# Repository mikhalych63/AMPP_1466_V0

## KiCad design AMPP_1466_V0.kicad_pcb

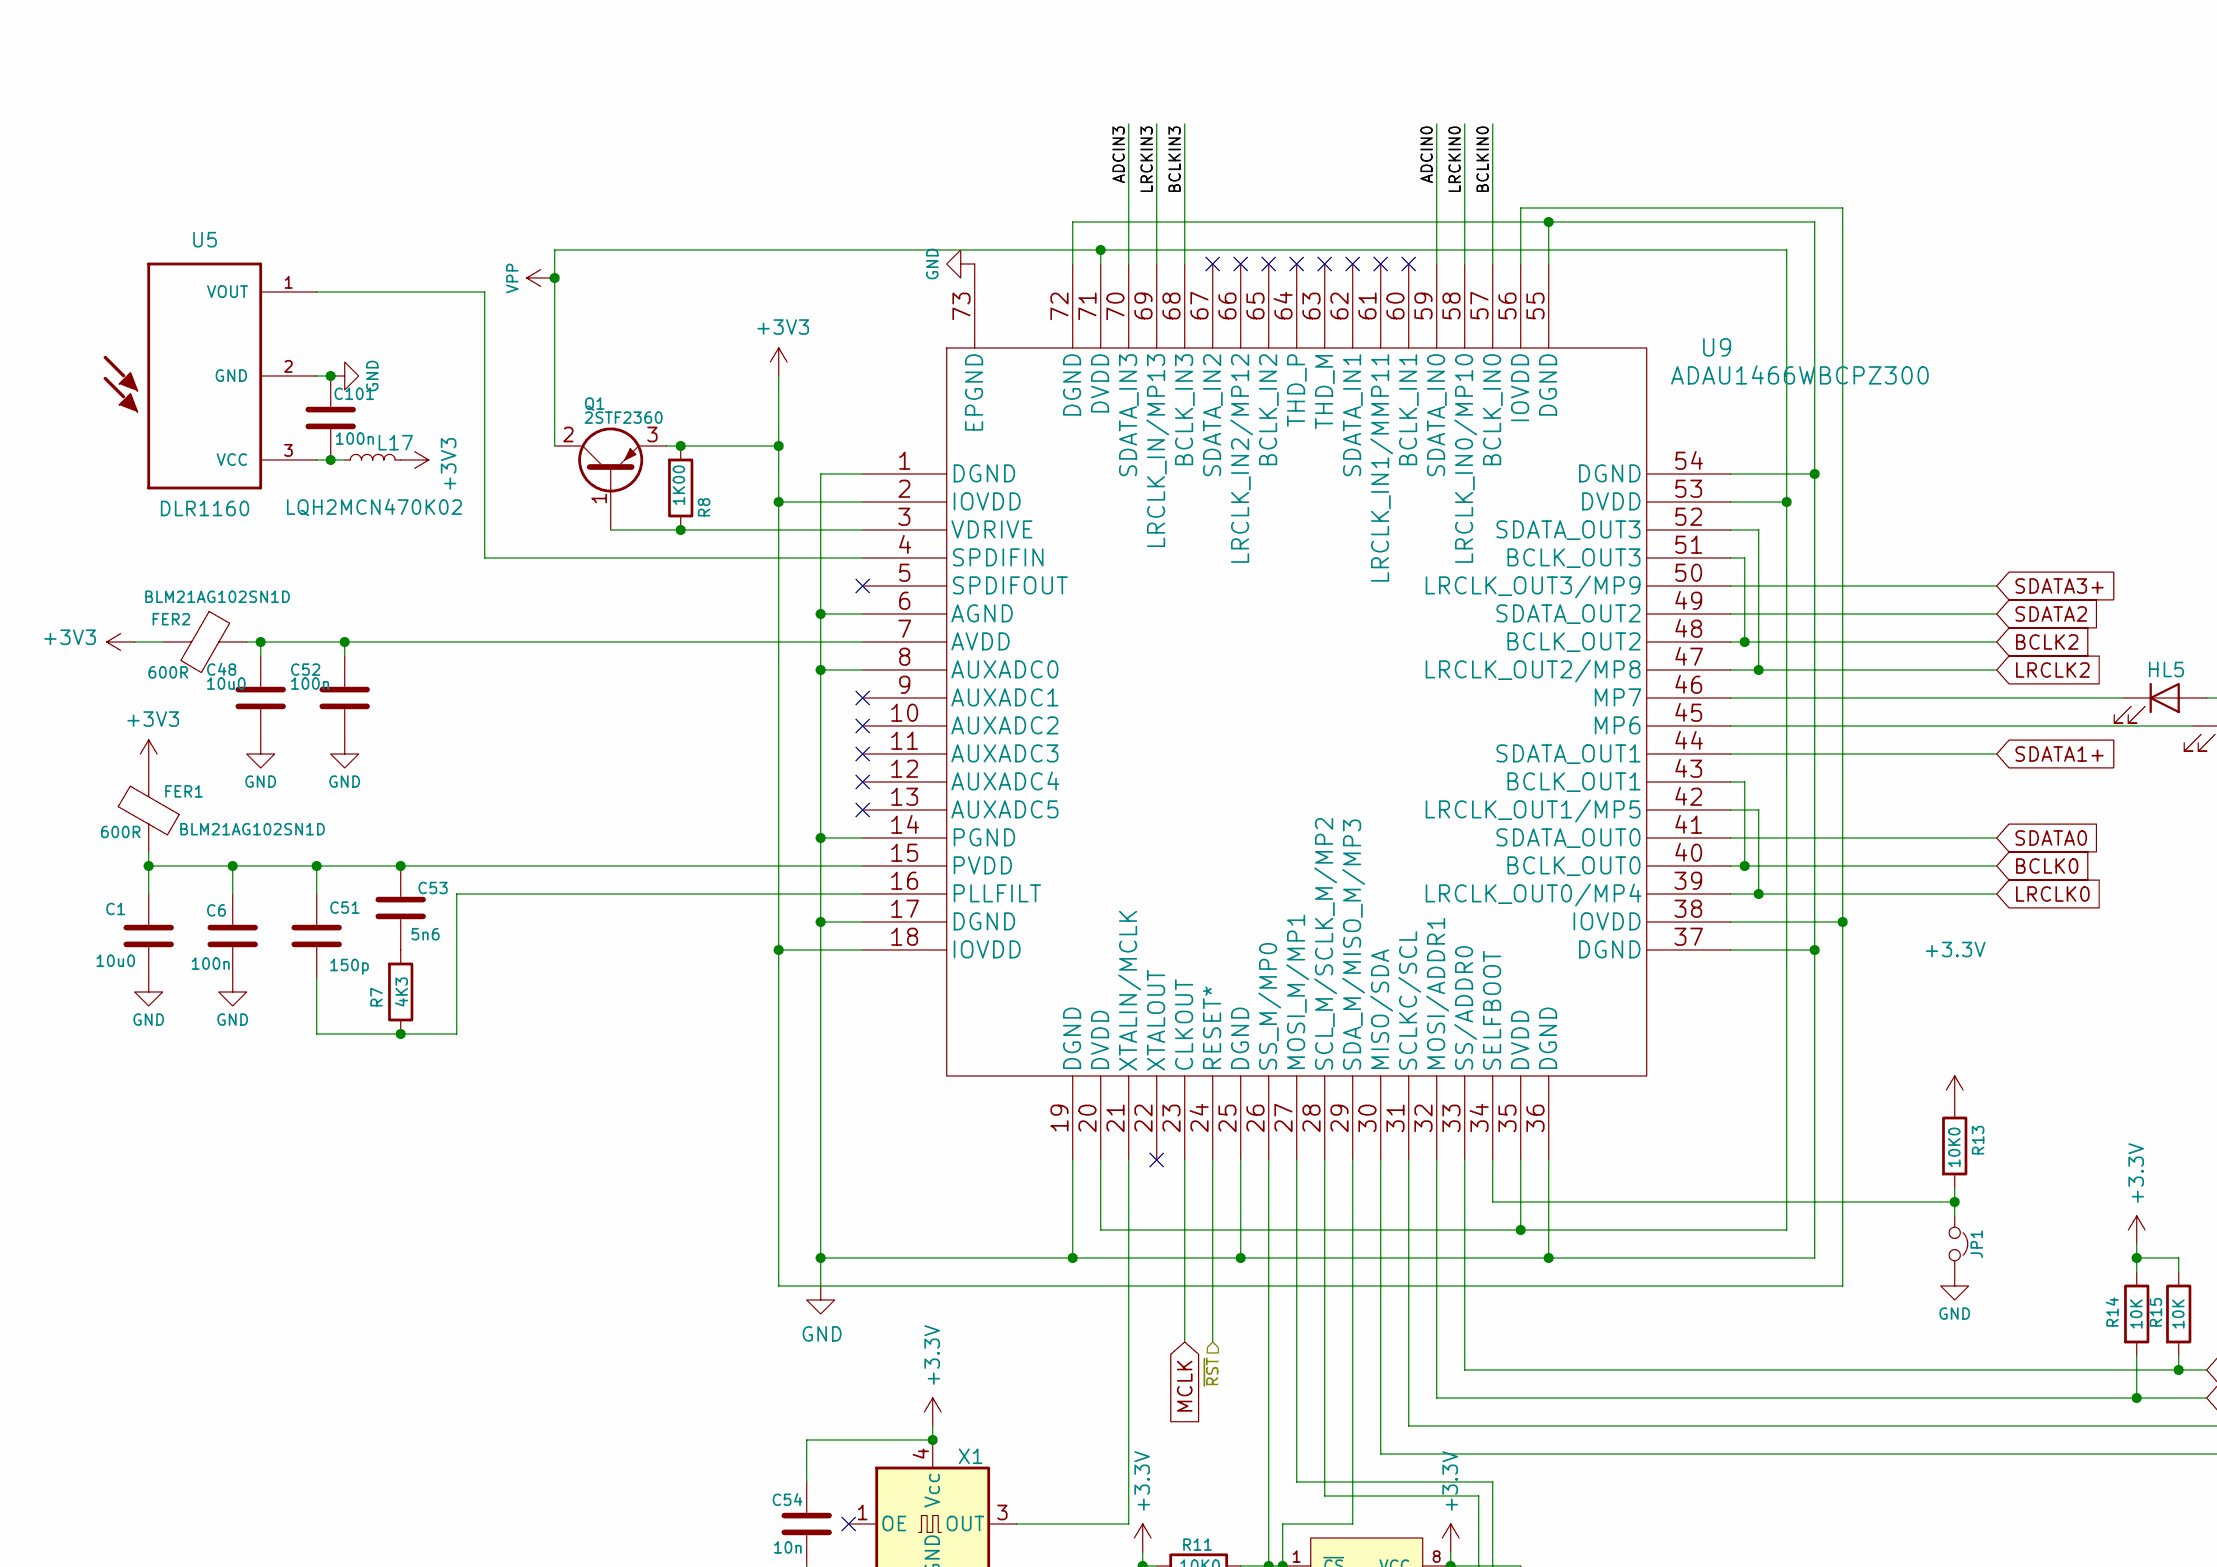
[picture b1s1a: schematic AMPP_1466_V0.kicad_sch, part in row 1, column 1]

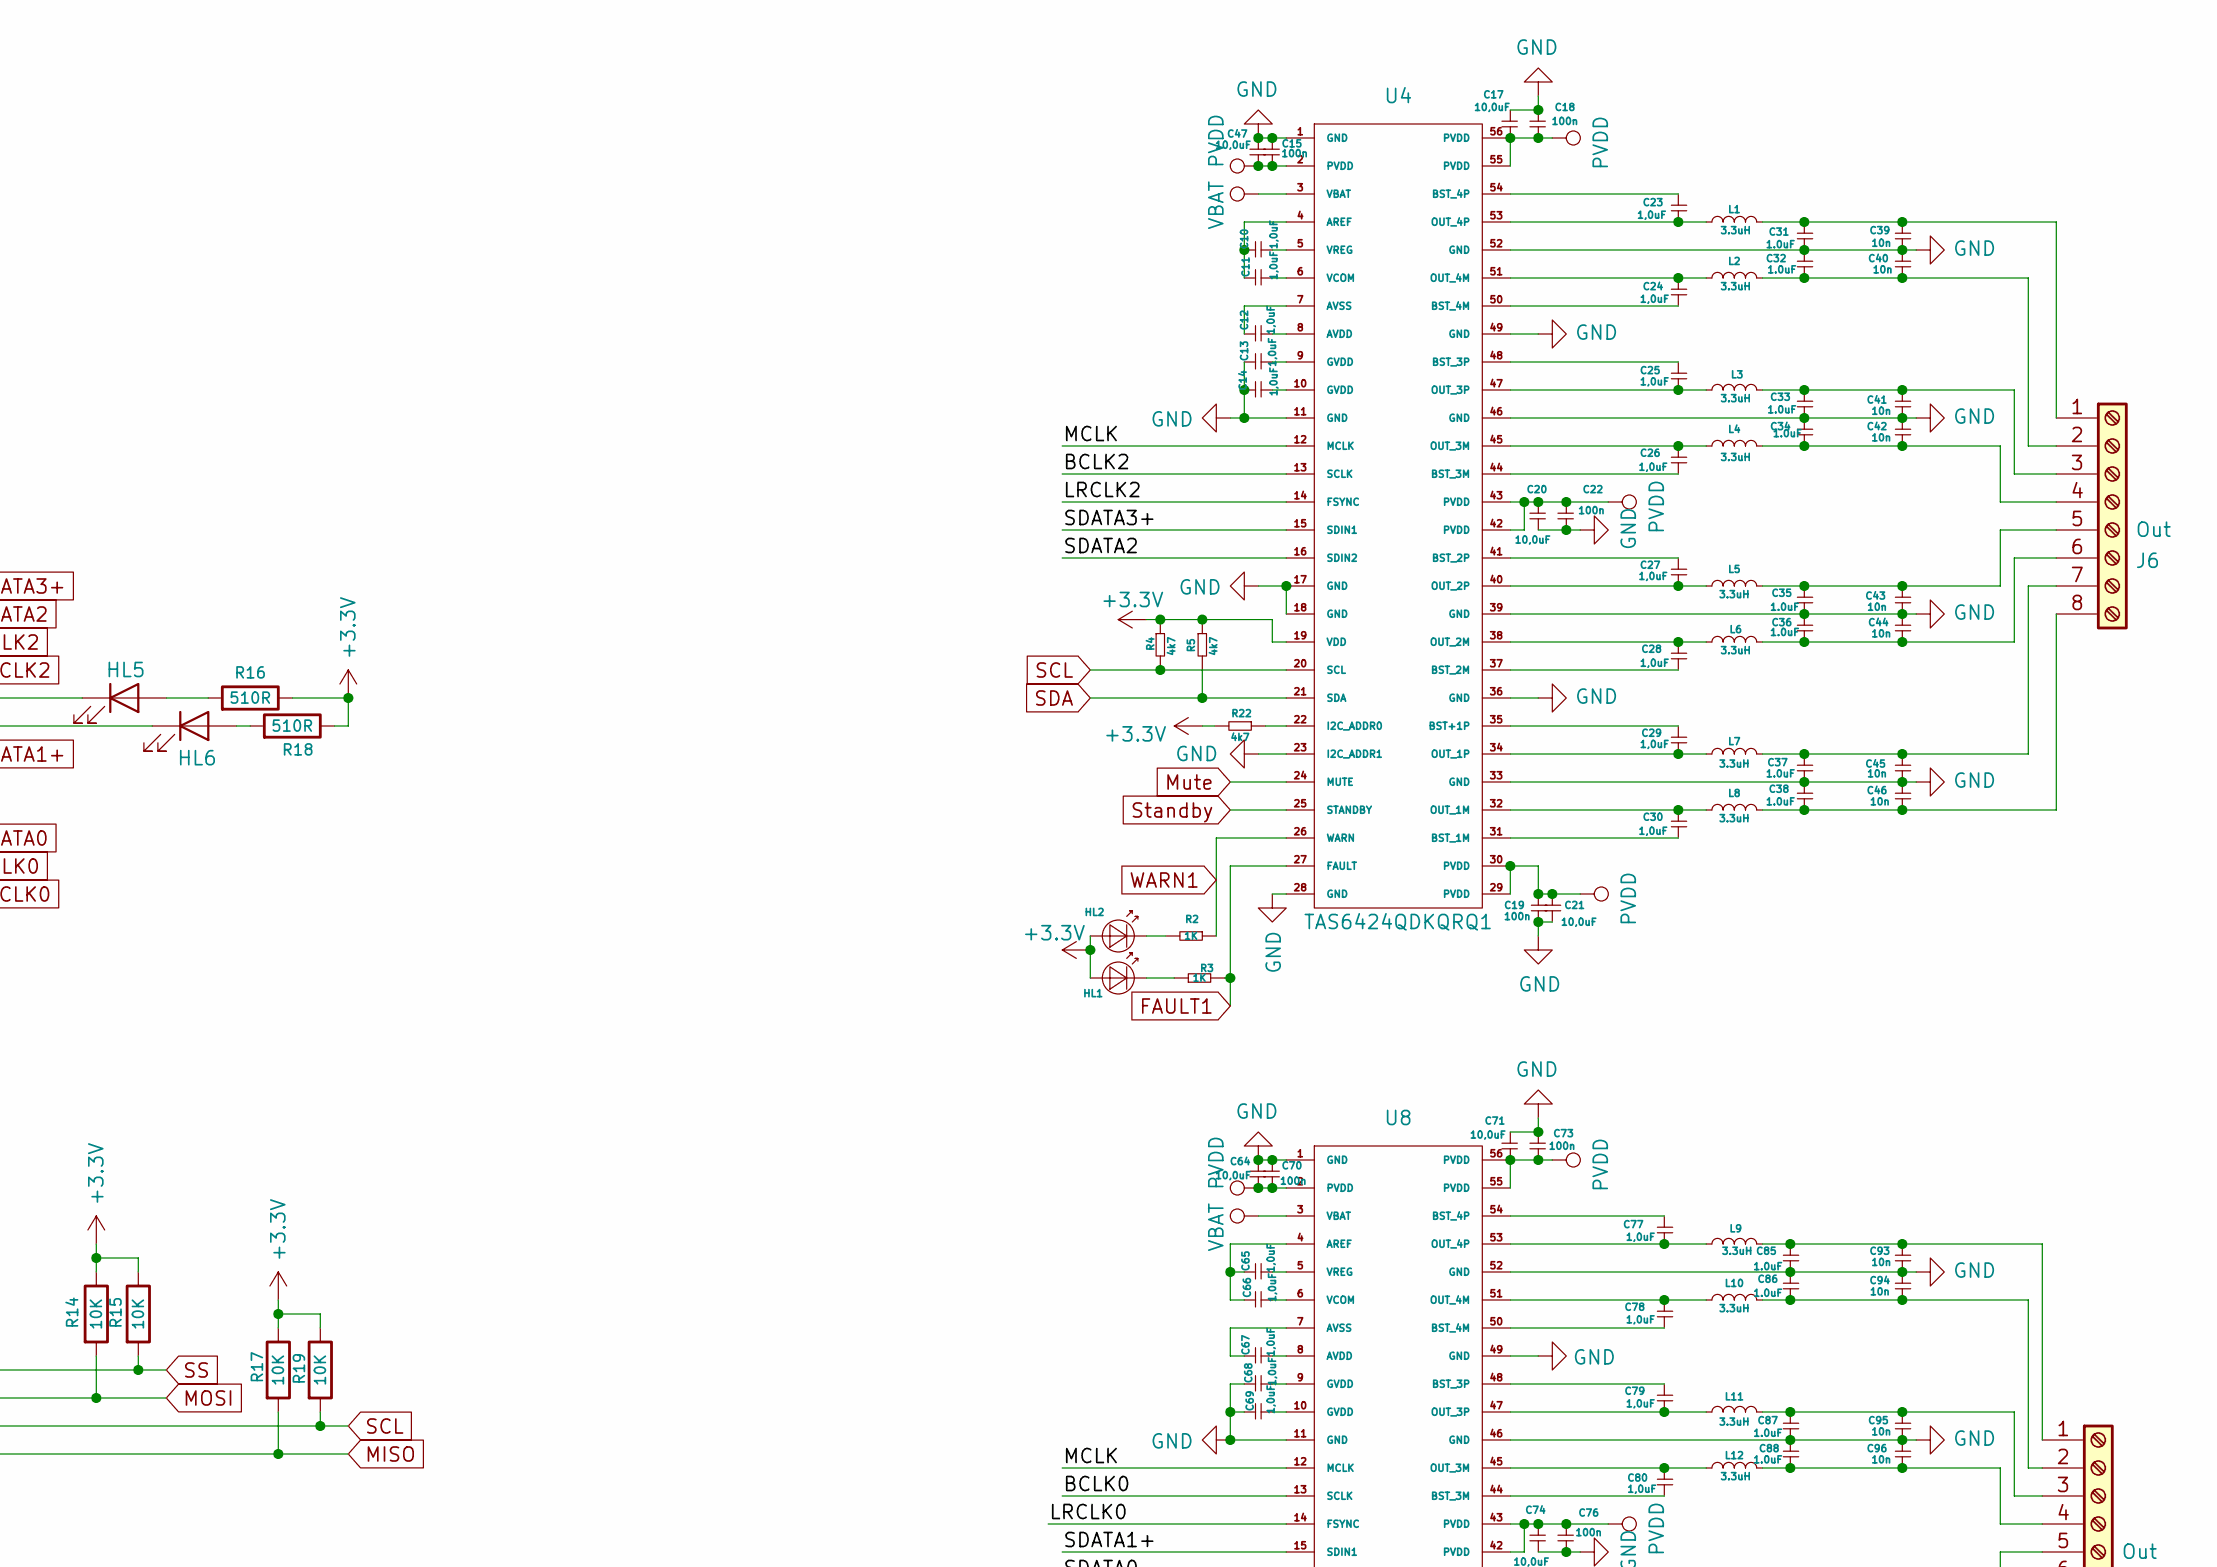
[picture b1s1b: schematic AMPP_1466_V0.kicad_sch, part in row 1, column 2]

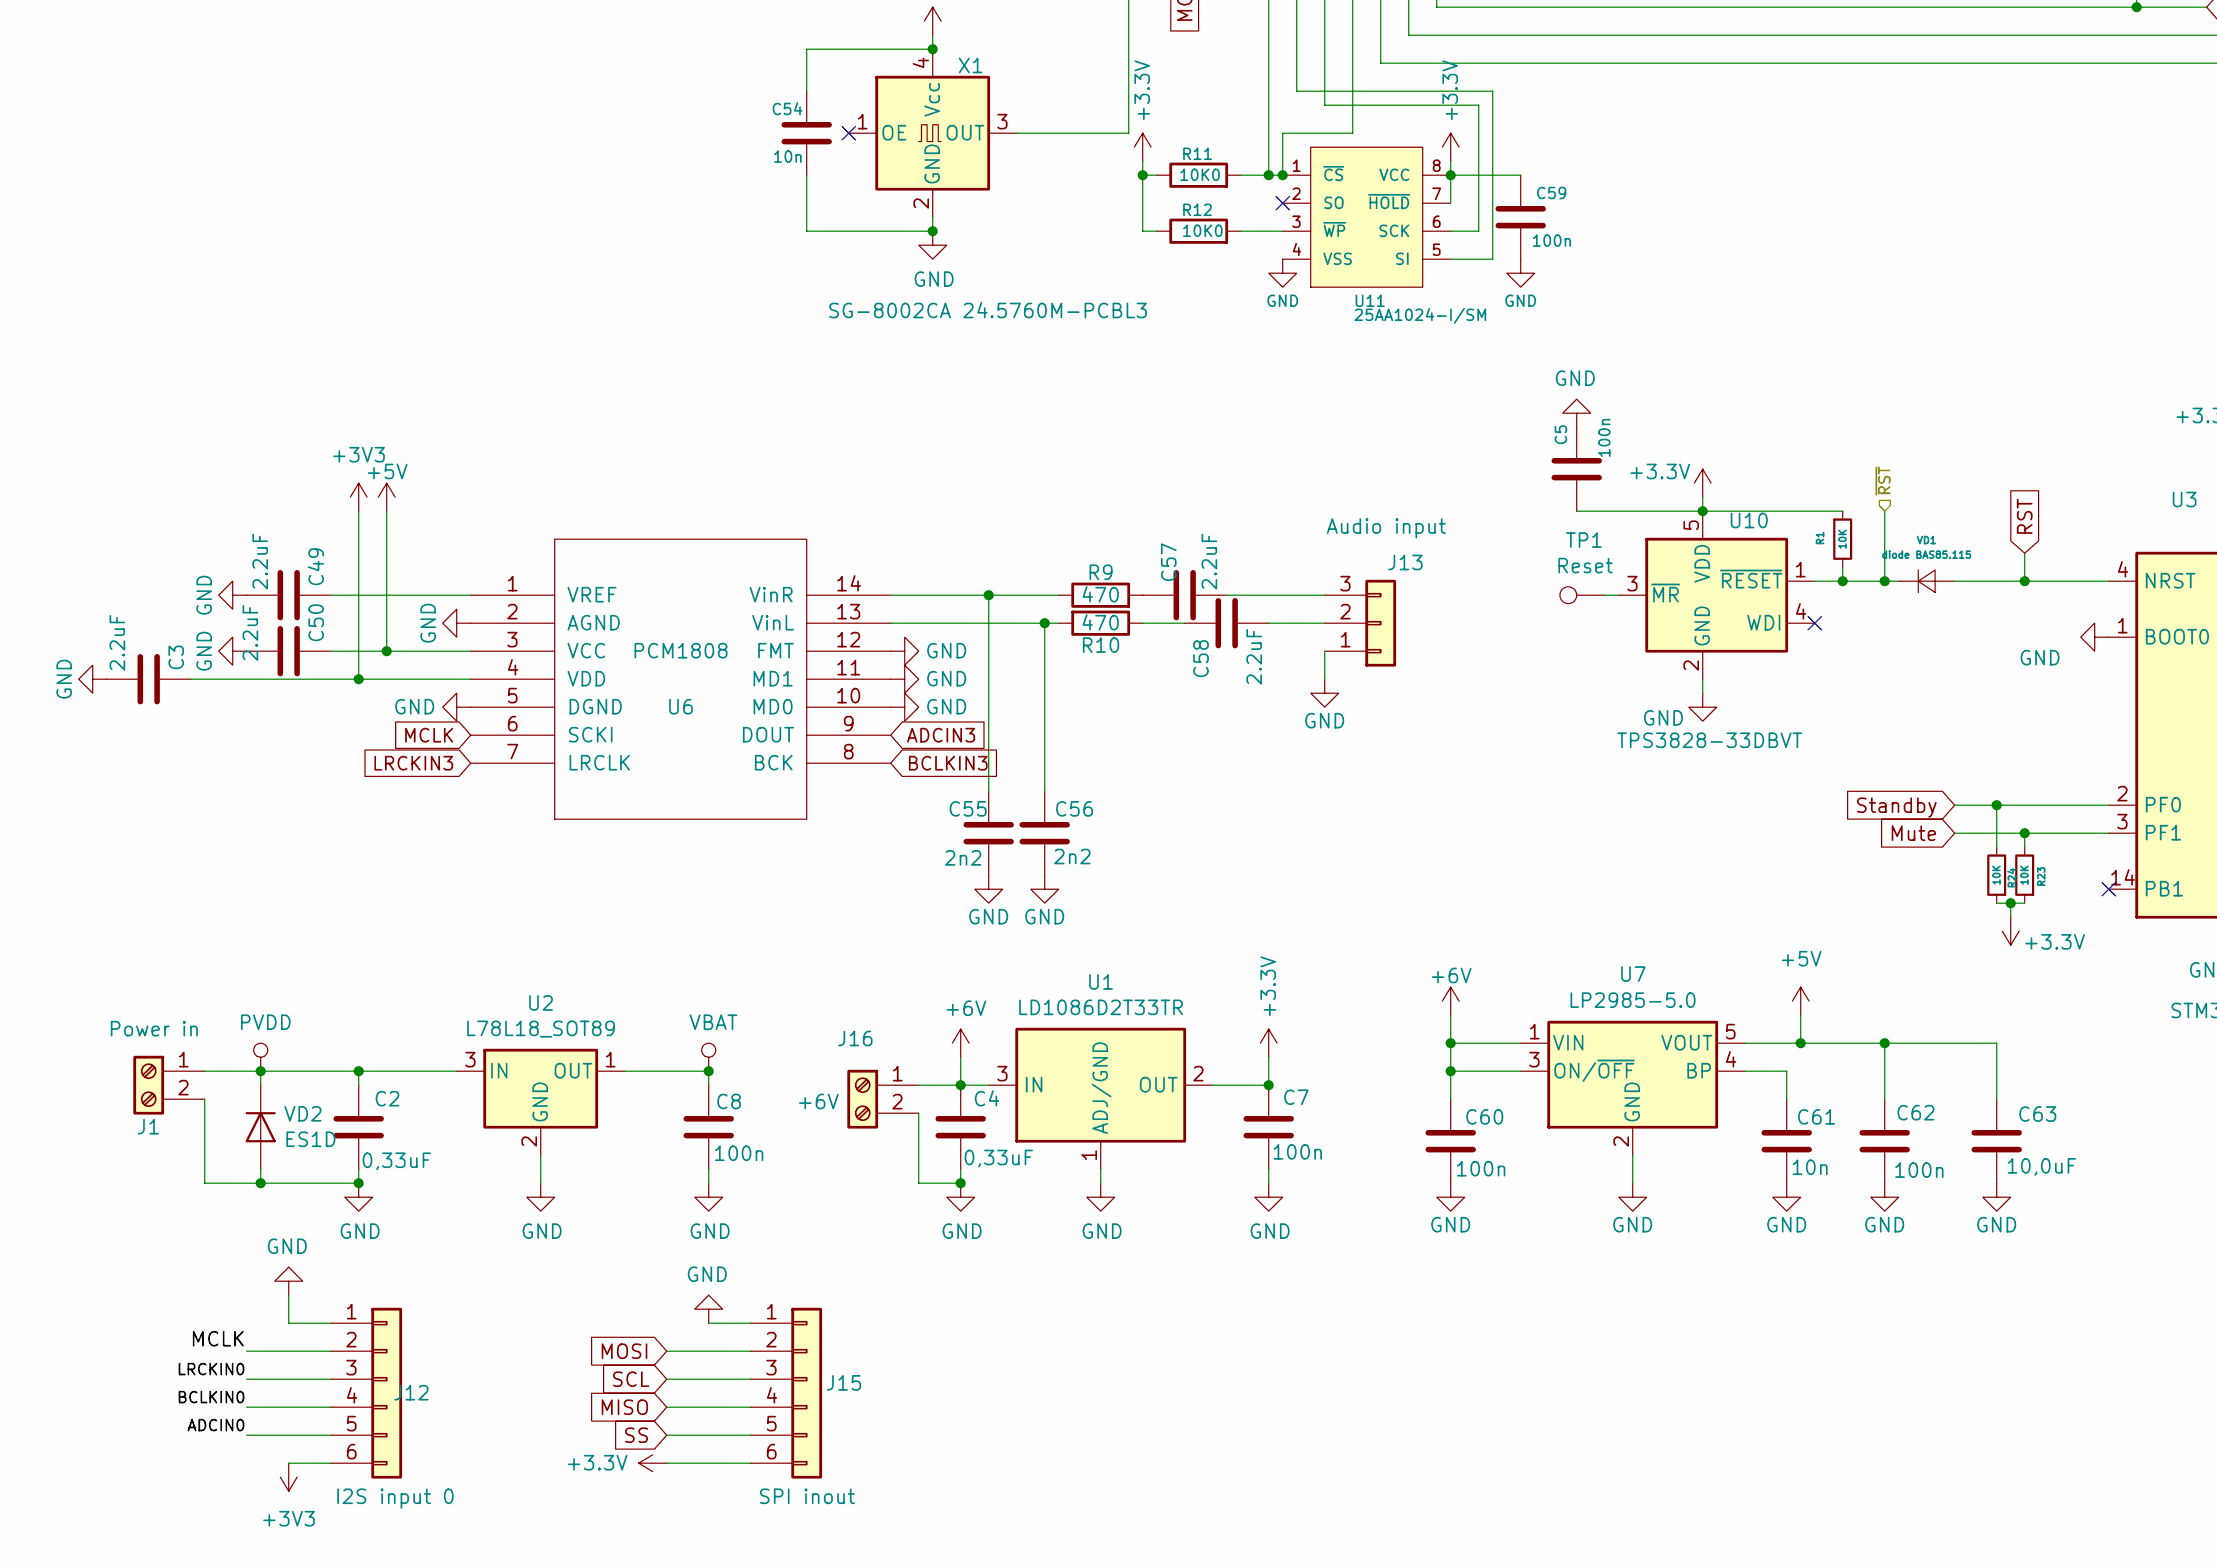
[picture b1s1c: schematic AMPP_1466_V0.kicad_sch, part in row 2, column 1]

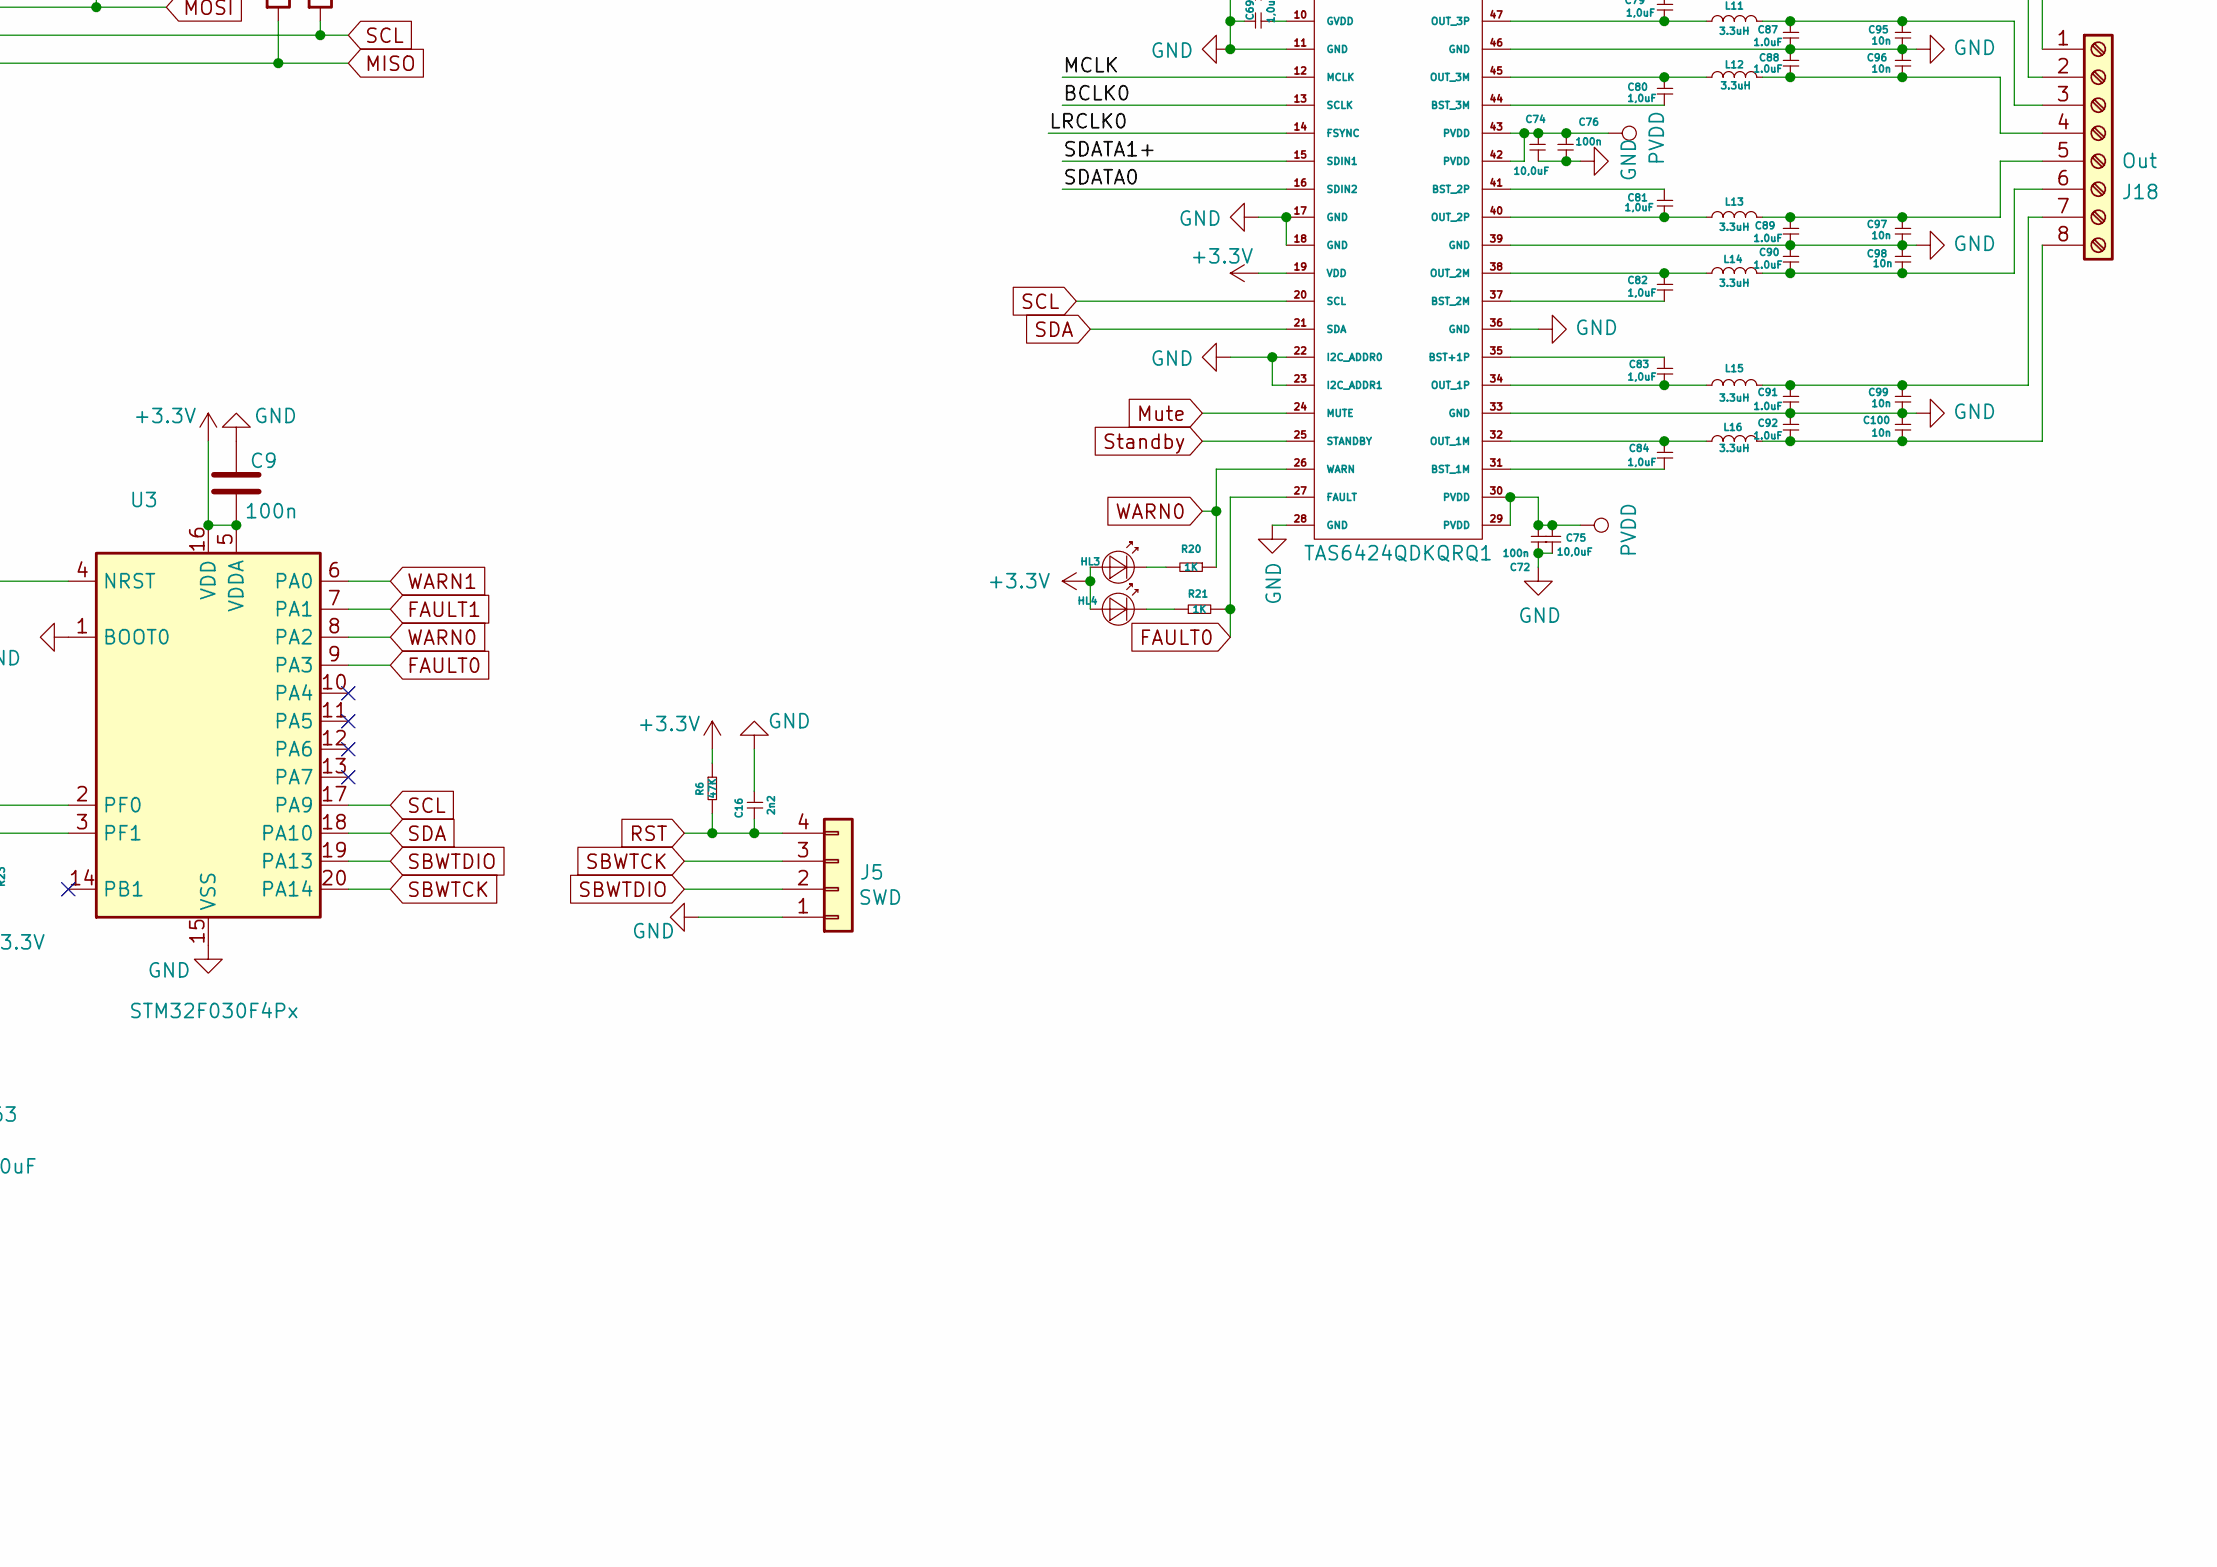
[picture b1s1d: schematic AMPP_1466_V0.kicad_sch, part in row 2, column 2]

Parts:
C1, C48: CAP_10u0_25V_X5R_0805; C_0805_2012Metric; digikey 490-10748-1-ND
C2, C4: 0,33uF; C_0603_1608Metric
C3, C49, C50, C57, C58: 2.2uF; C_0805_2012Metric
C5, C6, C52, C59: CAP_100n_50V_X7R_0603; C_0603_1608Metric; digikey 399-1170-1-ND
C7, C8, C9, C15, C18, C19, C22, C60, C62, C70, C72, C73, C76: 100n; C_0603_1608Metric
C10, C11, C12, C13, C14, C23, C24, C25, C26, C27, C28, C29, C30, C65, C66, C67, C68, C69, C77, C78, C79, C80, C81, C82, C83, C84: 1,0uF; C_0603_1608Metric
C16, C55, C56: 2n2; C_0603_1608Metric
C17, C20, C21, C47, C64, C71, C74, C75: 10,0uF; C_1206_3216Metric
C31, C32, C33, C34, C35, C36, C37, C38, C85, C86, C87, C88, C89, C90, C91, C92: 1.0uF; C_0805_2012Metric
C39, C40, C41, C42, C43, C44, C45, C46, C61, C93, C94, C95, C96, C97, C98, C99, C100: 10n; C_0603_1608Metric
C51: CAP_150p_50V_C0G_0603; C_0603_1608Metric; digikey 399-1125-1-ND
C53: CAP_5n6_50V_X7R_0603; C_0603_1608Metric; digikey 311-1134-1-ND
C54: CAP_10n_50V_X7R_0603; C_0603_1608Metric; digikey 399-1125-1-ND
C63: 10,0uF; C_0805_2012Metric
C101: CAP_100n_50V_X7R_0603; C_0603_1608Metric
FER1, FER2: BLM21AG102SN1D; R_0805_2012Metric_Pad1.15x1.40mm_HandSolder; digikey 490-1040-1-ND
HL1, HL4: LED_SMD_0603_YELLOW; LED_0603_1608Metric
HL2, HL3: LED_SMD_0603_RED; LED_0603_1608Metric
HL5, HL6: LED_SMD_0603_BLUE; LED_0603_1608Metric_Pad1.05x0.95mm_HandSolder
J1: Power in; DG16S-B-02P-13-00A(H)
J5: SWD; JST_XH_B4B-XH-A_1x04_P2.50mm_Vertical
J6, J18: Out; DG16S-B-08P-13-00A(H)
J12, J15: Conn_01x06_Male; JST_XH_B6B-XH-A_1x06_P2.50mm_Vertical
J13: Conn_01x03_Male; jack_3.5_pj313d-smt
J16: +6V; TerminalBlock_Phoenix_MKDS-1,5-2-5.08_1x02_P5.08mm_Horizont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
JP1: CON_JUMPER; R_0603_1608Metric_Pad1.05x0.95mm_HandSolder; digikey 732-5315-ND
L1, L2, L3, L4, L5, L6, L7, L8, L9, L10, L11, L12, L13, L14, L15, L16: 3.3uH; Panasonic_ETQP_5.5x5.0x3.0
L17: LQH2MCN470K02; L_Murata_LQH2MCNxxxx02_2.0x1.6mm
Q1: 2STF2360; SOT-89-3; digikey 497-7465-1-ND
R1, R23, R24: 10K; R_0603_1608Metric
R2, R3, R20, R21: 1K; R_0603_1608Metric
R4, R5, R22: 4k7; R_0603_1608Metric
R6: 47K; R_0603_1608Metric
R7: RES_4K7_1%_0.125W_Thick_0603; R_0603_1608Metric; digikey 311-4.32KCRCT-ND
R8: RES_1K0_1%_0.125W_Thick_0603; R_0603_1608Metric; digikey 311-1.00KCRCT-ND
R9, R10: 470; R_0603_1608Metric
R11, R12, R13: RES_10K0_1%_0.125W_Thick_0603; R_0603_1608Metric; digikey 311-10.0KCRCT-ND
R14, R15, R17, R19: RES_10K0_1%_0.125W_Thick_0603; R_0603_1608Metric
R16, R18: RES_51R0_1%_0.125W_Thick_0603; R_0603_1608Metric; digikey 311-51.0CRCT-ND
TP1: Reset; TestPoint_Pad_D1.5mm
U1: LD1086D2T33TR; TO-263-2
U2: L78L18_SOT89; SOT-89-3
U3: STM32F030F4Px; TSSOP-20_4.4x6.5mm_P0.65mm
U4, U8: TAS6424QDKQRQ1; SSOP-56_7.5x18.5mm_P0.635mm
U5: DLR1160; Toslink
U6: PCM1808; TSSOP-14_4.4x5mm_P0.65mm
U7: LP2985-5.0; SOT-23-5
U9: ADAU1466WBCPZ300
U10: TPS3828-33DBVT; SOT-23-5
U11: 25AA1024-I/SM; SOIC-8_3.9x4.9mm_P1.27mm; digikey 25AA1024T-I/SMCT-ND
VD1: diode BAS85.115; sod80c
VD2: ES1D; do214ac
X1: SG-8002CA 24.5760M-PCBL3; Oscillator_SMD_SeikoEpson_SG8002CA-4Pin_7.0x5.0mm

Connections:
+5V: C50.1, C62.2, C63.1, U6.3 (VCC), U7.5 (VOUT)
+6V: C4.1, C60.2, J16.1, U1.3 (IN), U7.1 (VIN), U7.3 (ON/~OFF)
/ADCIN0: J12.5, U9.59 (SDATA_IN0)
/BCLKIN0: J12.4, U9.57 (BCLK_IN0)
/LRCKIN0: J12.3, U9.58 (LRCLK_IN0/MP10)
/~RST: R1.2, U9.24 (RESET*), U10.1 (~RESET), VD1.1 (K)
ADCIN3: U6.9 (DOUT), U9.70 (SDATA_IN3)
BCLK0: U8.13 (SCLK), U9.40 (BCLK_OUT0), U9.43 (BCLK_OUT1)
BCLK2: U4.13 (SCLK), U9.48 (BCLK_OUT2), U9.51 (BCLK_OUT3)
BCLKIN3: U6.8 (BCK), U9.68 (BCLK_IN3)
FAULT0: R21.2, U3.9 (PA3), U8.27 (FAULT)
FAULT1: R3.2, U3.7 (PA1), U4.27 (FAULT)
LRCKIN3: U6.7 (LRCLK), U9.69 (LRCLK_IN/MP13)
LRCLK0: U8.14 (FSYNC), U9.39 (LRCLK_OUT0/MP4), U9.42 (LRCLK_OUT1/MP5)
LRCLK2: U4.14 (FSYNC), U9.47 (LRCLK_OUT2/MP8), U9.52 (SDATA_OUT3)
MCLK: J12.2, U4.12 (MCLK), U6.6 (SCKI), U8.12 (MCLK), U9.23 (CLKOUT)
MISO: J15.4, R17.2, U9.30 (MISO/SDA)
MOSI: J15.2, R14.2, U9.32 (MOSI/ADDR1)
Mute: R23.2, U3.3 (PF1), U4.24 (MUTE), U8.24 (MUTE)
unnamed: C1.1, C6.1, C51.1, C53.1, FER1.1, U9.15 (PVDD)
unnamed: C10.1, U4.5 (VREG)
unnamed: C10.2, C11.2, U4.4 (AREF)
unnamed: C11.1, U4.6 (VCOM)
unnamed: C12.1, U4.8 (AVDD)
unnamed: C12.2, U4.7 (AVSS)
unnamed: C13.1, U4.9 (GVDD)
unnamed: C14.1, U4.10 (GVDD)
unnamed: C23.1, L1.1, U4.53 (OUT_4P)
unnamed: C23.2, U4.54 (BST_4P)
unnamed: C24.1, U4.50 (BST_4M)
unnamed: C24.2, L2.1, U4.51 (OUT_4M)
unnamed: C25.1, L3.1, U4.47 (OUT_3P)
unnamed: C25.2, U4.48 (BST_3P)
unnamed: C26.1, U4.44 (BST_3M)
unnamed: C26.2, L4.1, U4.45 (OUT_3M)
unnamed: C27.1, L5.1, U4.40 (OUT_2P)
unnamed: C27.2, U4.41 (BST_2P)
unnamed: C28.1, U4.37 (BST_2M)
unnamed: C28.2, L6.1, U4.38 (OUT_2M)
unnamed: C29.1, L7.1, U4.34 (OUT_1P)
unnamed: C29.2, U4.35 (BST+1P)
unnamed: C30.1, U4.31 (BST_1M)
unnamed: C30.2, L8.1, U4.32 (OUT_1M)
unnamed: C31.2, C39.2, J6.1, L1.2
unnamed: C32.1, C40.1, J6.2, L2.2
unnamed: C33.2, C41.2, J6.3, L3.2
unnamed: C34.1, C42.1, J6.4, L4.2
unnamed: C35.2, C43.2, J6.5, L5.2
unnamed: C36.1, C44.1, J6.6, L6.2
unnamed: C37.2, C45.2, J6.7, L7.2
unnamed: C38.1, C46.1, J6.8, L8.2
unnamed: C48.1, C52.1, FER2.1, U9.7 (AVDD)
unnamed: C49.1, U6.1 (VREF)
unnamed: C51.2, R7.1, U9.16 (PLLFILT)
unnamed: C53.2, R7.2
unnamed: C55.2, R9.1, U6.14 (VinR)
unnamed: C56.2, R10.2, U6.13 (VinL)
unnamed: C57.1, J13.3
unnamed: C57.2, R9.2
unnamed: C58.1, R10.1
unnamed: C58.2, J13.2
unnamed: C61.2, U7.4 (BP)
unnamed: C65.1, U8.5 (VREG)
unnamed: C65.2, C66.2, U8.4 (AREF)
unnamed: C66.1, U8.6 (VCOM)
unnamed: C67.1, U8.8 (AVDD)
unnamed: C67.2, U8.7 (AVSS)
unnamed: C68.1, U8.9 (GVDD)
unnamed: C69.1, U8.10 (GVDD)
unnamed: C77.1, L9.1, U8.53 (OUT_4P)
unnamed: C77.2, U8.54 (BST_4P)
unnamed: C78.1, U8.50 (BST_4M)
unnamed: C78.2, L10.1, U8.51 (OUT_4M)
unnamed: C79.1, L11.1, U8.47 (OUT_3P)
unnamed: C79.2, U8.48 (BST_3P)
unnamed: C80.1, U8.44 (BST_3M)
unnamed: C80.2, L12.1, U8.45 (OUT_3M)
unnamed: C81.1, L13.1, U8.40 (OUT_2P)
unnamed: C81.2, U8.41 (BST_2P)
unnamed: C82.1, U8.37 (BST_2M)
unnamed: C82.2, L14.1, U8.38 (OUT_2M)
unnamed: C83.1, L15.1, U8.34 (OUT_1P)
unnamed: C83.2, U8.35 (BST+1P)
unnamed: C84.1, U8.31 (BST_1M)
unnamed: C84.2, L16.1, U8.32 (OUT_1M)
unnamed: C85.2, C93.2, J18.1, L9.2
unnamed: C86.1, C94.1, J18.2, L10.2
unnamed: C87.2, C95.2, J18.3, L11.2
unnamed: C88.1, C96.1, J18.4, L12.2
unnamed: C89.2, C97.2, J18.5, L13.2
unnamed: C90.1, C98.1, J18.6, L14.2
unnamed: C91.2, C99.2, J18.7, L15.2
unnamed: C92.1, C100.1, J18.8, L16.2
unnamed: C101.2, L17.1, U5.3 (VCC)
unnamed: HL1.1 (K), R3.1
unnamed: HL3.1 (K), R20.2
unnamed: HL4.1 (K), R21.1
unnamed: HL5.1 (K), U9.46 (MP7)
unnamed: HL5.2 (A), R16.2
unnamed: HL6.1 (K), U9.45 (MP6)
unnamed: HL6.2 (A), R18.2
unnamed: JP1.1, R13.2, U9.34 (SELFBOOT)
unnamed: Q1.1 (B), R8.1, U9.3 (VDRIVE)
unnamed: HL2.1 (K), R2.2
unnamed: R11.2, U9.26 (SS_M/MP0), U9.29 (SDA_M/MISO_M/MP3), U11.1 (~CS)
unnamed: R12.2, U11.3 (~WP)
unnamed: R22.1, U4.22 (I2C_ADDR0)
unnamed: TP1.1, U10.3 (~MR)
unnamed: U5.1 (VOUT), U9.4 (SPDIFIN)
unnamed: U9.21 (XTALIN/MCLK), X1.3 (OUT)
unnamed: U9.27 (MOSI_M/MP1), U11.5 (SI)
unnamed: U9.28 (SCL_M/SCLK_M/MP2), U11.6 (SCK)
PVDD: C2.1, C15.2, C17.2, C18.2, C19.2, C20.1, C21.2, C22.1, C47.2, C64.2, C70.2, C71.2, C72.2, C73.2, C74.1, C75.2, C76.1, J1.1, U2.3 (IN), U4.2 (PVDD), U4.29 (PVDD), U4.30 (PVDD), U4.42 (PVDD), U4.43 (PVDD), U4.55 (PVDD), U4.56 (PVDD), U8.2 (PVDD), U8.29 (PVDD), U8.30 (PVDD), U8.42 (PVDD), U8.43 (PVDD), U8.55 (PVDD), U8.56 (PVDD), VD2.1 (K)
RST: C16.1, J5.4, R6.2, U3.4 (NRST), VD1.2 (A)
SBWTCK: J5.3, U3.20 (PA14)
SBWTDIO: J5.2, U3.19 (PA13)
SCL: R4.2, U3.17 (PA9), U4.20 (SCL), U8.20 (SCL)
SCL: J15.3, R19.2, U9.31 (SCLKC/SCL)
SDA: R5.2, U3.18 (PA10), U4.21 (SDA), U8.21 (SDA)
SDATA0: U8.16 (SDIN2), U9.41 (SDATA_OUT0)
SDATA1+: U8.15 (SDIN1), U9.44 (SDATA_OUT1)
SDATA2: U4.16 (SDIN2), U9.49 (SDATA_OUT2)
SDATA3+: U4.15 (SDIN1), U9.50 (LRCLK_OUT3/MP9)
SS: J15.5, R15.2, U9.33 (SS/ADDR0)
Standby: R24.2, U3.2 (PF0), U4.25 (STANDBY), U8.25 (STANDBY)
VBAT: C8.1, U2.1 (OUT), U4.3 (VBAT), U8.3 (VBAT)
VPP: Q1.2 (C), U9.20 (DVDD), U9.35 (DVDD), U9.53 (DVDD), U9.71 (DVDD)
WARN0: R20.1, U3.8 (PA2), U8.26 (WARN)
WARN1: R2.1, U3.6 (PA0), U4.26 (WARN)

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
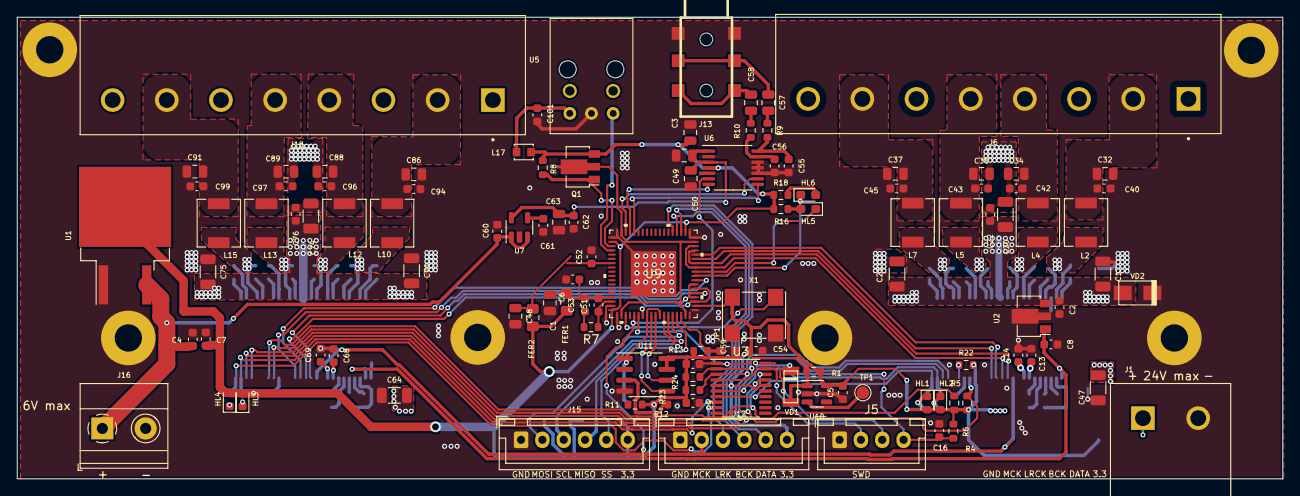
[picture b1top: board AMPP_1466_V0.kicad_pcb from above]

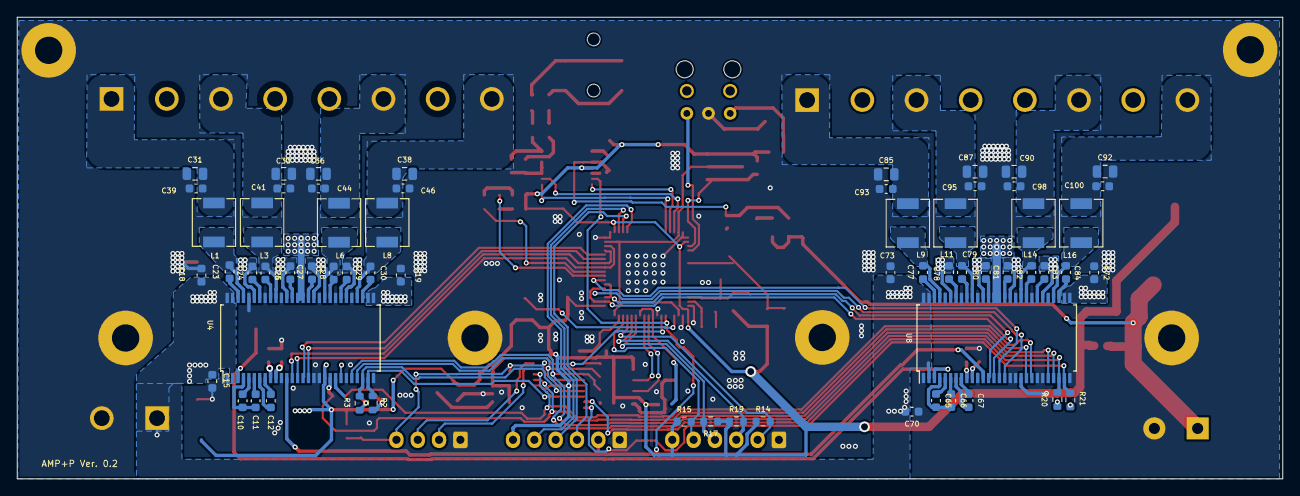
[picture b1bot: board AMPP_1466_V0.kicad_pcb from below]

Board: 2 copper layers, 148.3 x 54.1 mm, 175 parts (62 on the bottom side), 131 nets.

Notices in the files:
parts and their libraries:
Copyright 2021 Accelerated Designs. All rights reserved.
